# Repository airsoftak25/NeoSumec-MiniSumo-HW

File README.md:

# NeoSumec-MiniSumo-HW

# Description 
In this reposirotry contains: PCB, Gerber, cut files and other stuff about elektronics for our Minisumo robots

|Folder name|what is it|
|:-:|:-|
|MK-1|Contains HW design for our first MiniSumo robot **MK-1**|
|QRE-Boards|Contains HW design for our QRE1113 sensor rigs|

# Contributors
People witch work on some part of HW for our MiniSumo Robots
| Name | Part |
|:-:|:-|
| Vadim Sobčuk | Head of PCB and cut Design |

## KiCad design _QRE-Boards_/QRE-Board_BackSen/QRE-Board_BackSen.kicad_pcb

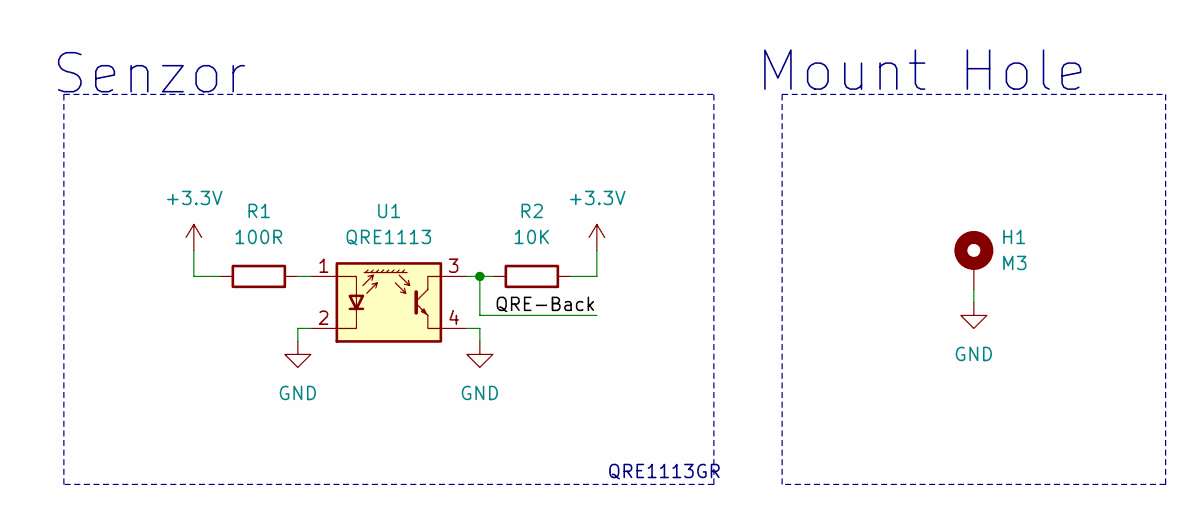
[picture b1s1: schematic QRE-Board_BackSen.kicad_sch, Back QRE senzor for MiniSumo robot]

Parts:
H1: M3; MountingHole_3.2mm_M3_Pad
R1: 100R; R_0805_2012Metric_Pad1.20x1.40mm_HandSolder
R2: 10K; C_0805_2012Metric_Pad1.18x1.45mm_HandSolder
U1: QRE1113; OnSemi_CASE100AQ

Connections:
+3.3V: R1.1, R2.2
/QRE-Back: R2.1, U1.3
GND: H1.1 (1_1), U1.2 (K), U1.4
unnamed: R1.2, U1.1 (A)

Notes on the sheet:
QRE1113GR
Mount Hole
Senzor

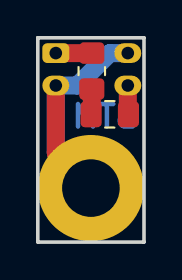
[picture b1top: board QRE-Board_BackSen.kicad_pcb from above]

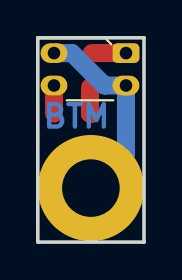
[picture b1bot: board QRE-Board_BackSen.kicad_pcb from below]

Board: 2 copper layers, 5.9 x 11.3 mm, 4 parts (2 on the bottom side), 4 nets.

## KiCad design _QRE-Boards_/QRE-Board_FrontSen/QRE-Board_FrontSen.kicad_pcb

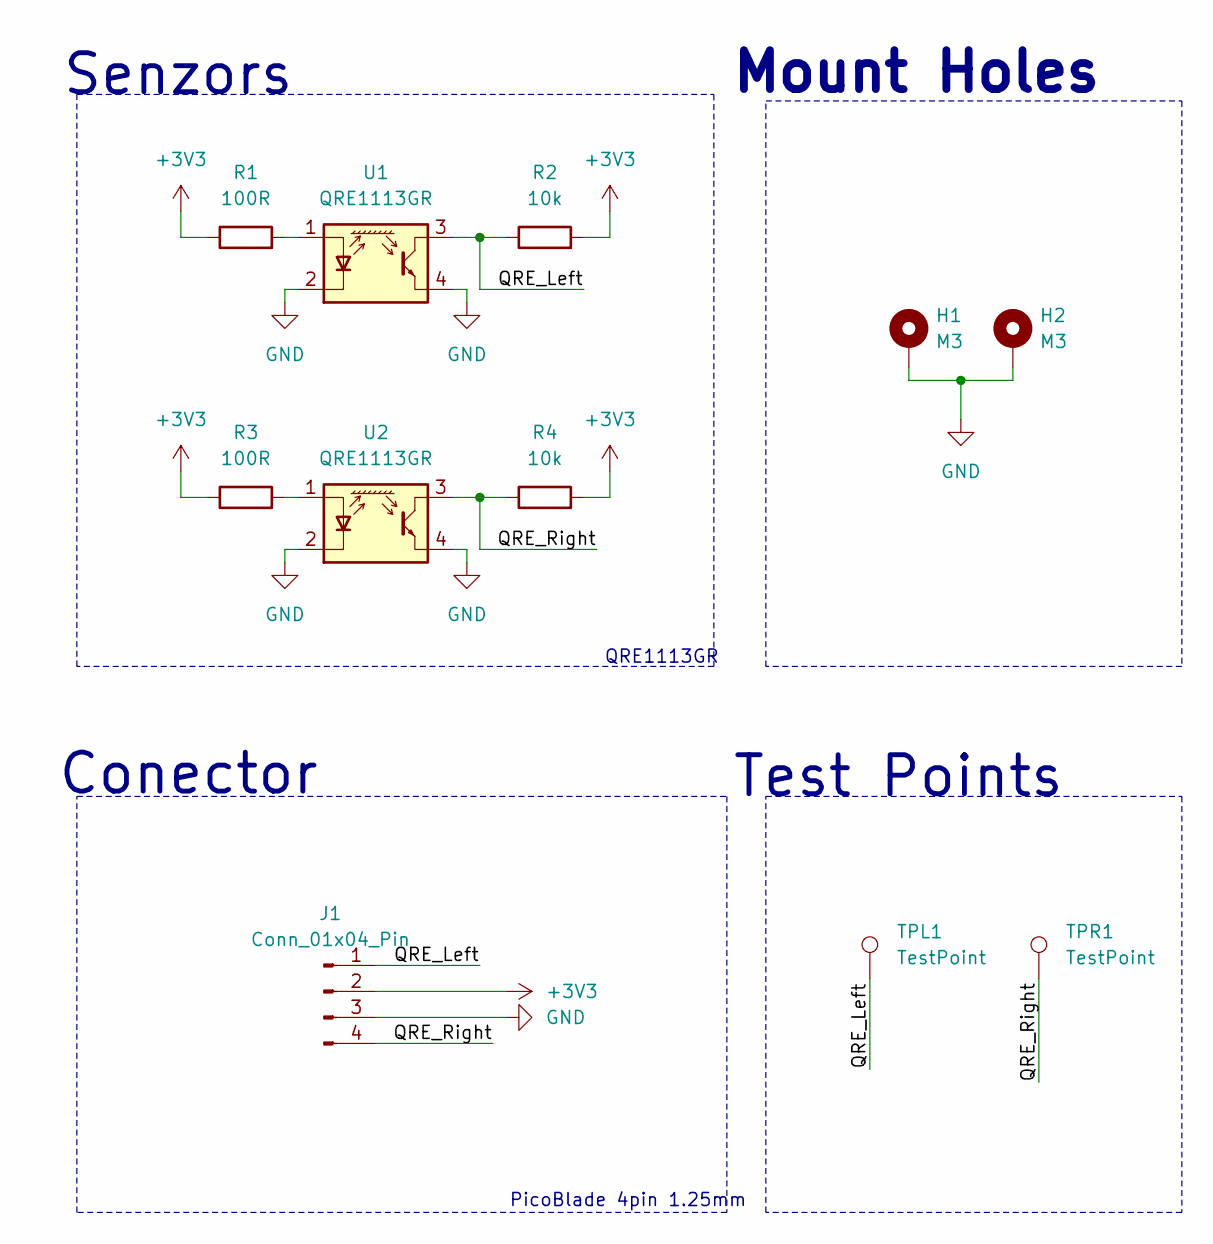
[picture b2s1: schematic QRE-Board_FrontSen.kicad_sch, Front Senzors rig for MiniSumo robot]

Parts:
H1, H2: M3; MountingHole_3.2mm_M3_Pad_Via
J1: Conn_01x04_Pin; Molex_PicoBlade_53261-0471_1x04-1MP_P1.25mm_Horizontal
R1, R3: 100R; R_0805_2012Metric_Pad1.20x1.40mm_HandSolder
R2, R4: 10k; R_0805_2012Metric_Pad1.20x1.40mm_HandSolder
TPL1: TestPoint
TPR1: TestPoint
U1, U2: QRE1113GR; OnSemi_CASE100CY

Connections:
+3V3: J1.2, R1.1, R2.2, R3.1, R4.2
/QRE_Left: J1.1, R2.1, TPL1.1 (1_1), U1.3
/QRE_Right: J1.4, R4.1, TPR1.1 (1_1), U2.3
GND: H1.1 (1_1), H2.1 (1_1), J1.3, U1.2 (K), U1.4, U2.2 (K), U2.4
unnamed: R1.2, U1.1 (A)
unnamed: R3.2, U2.1 (A)

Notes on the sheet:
Mount Holes
Conector
Test Points
PicoBlade 4pin 1.25mm
QRE1113GR
Senzors

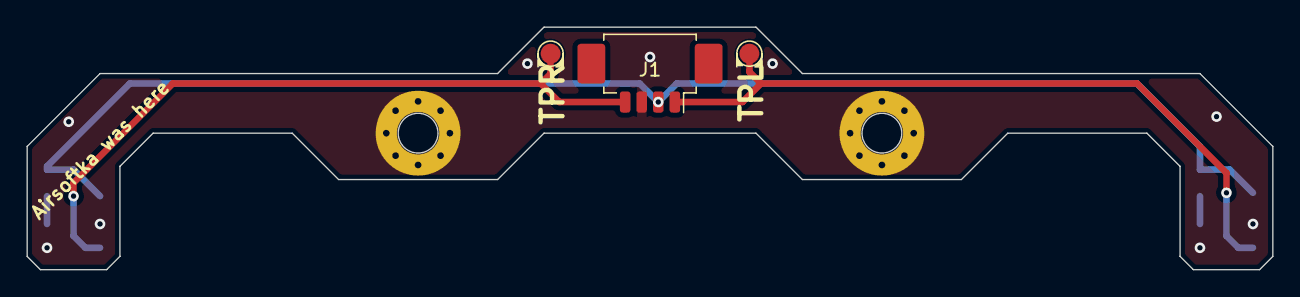
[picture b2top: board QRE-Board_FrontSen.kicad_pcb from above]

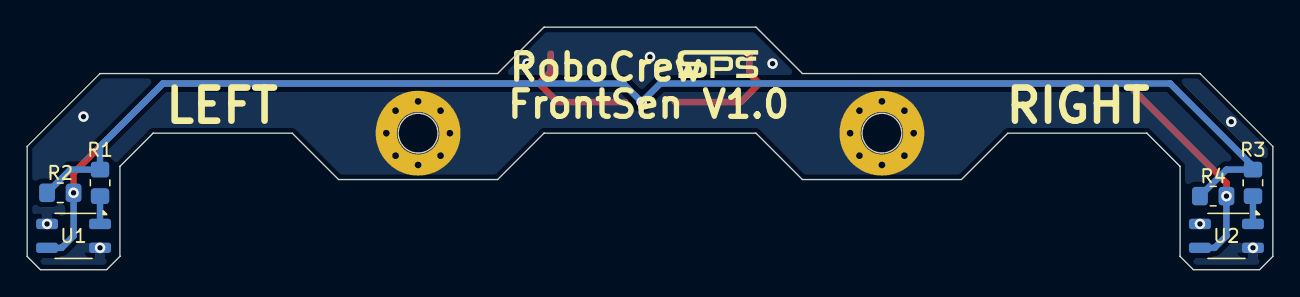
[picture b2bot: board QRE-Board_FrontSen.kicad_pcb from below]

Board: 2 copper layers, 94.0 x 18.3 mm, 11 parts (6 on the bottom side), 6 nets.

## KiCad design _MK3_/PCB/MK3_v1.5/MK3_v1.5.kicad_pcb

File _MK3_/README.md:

# This Folder contains upgrades for MK3(from Team Sumec) maded by Team NeoSumec

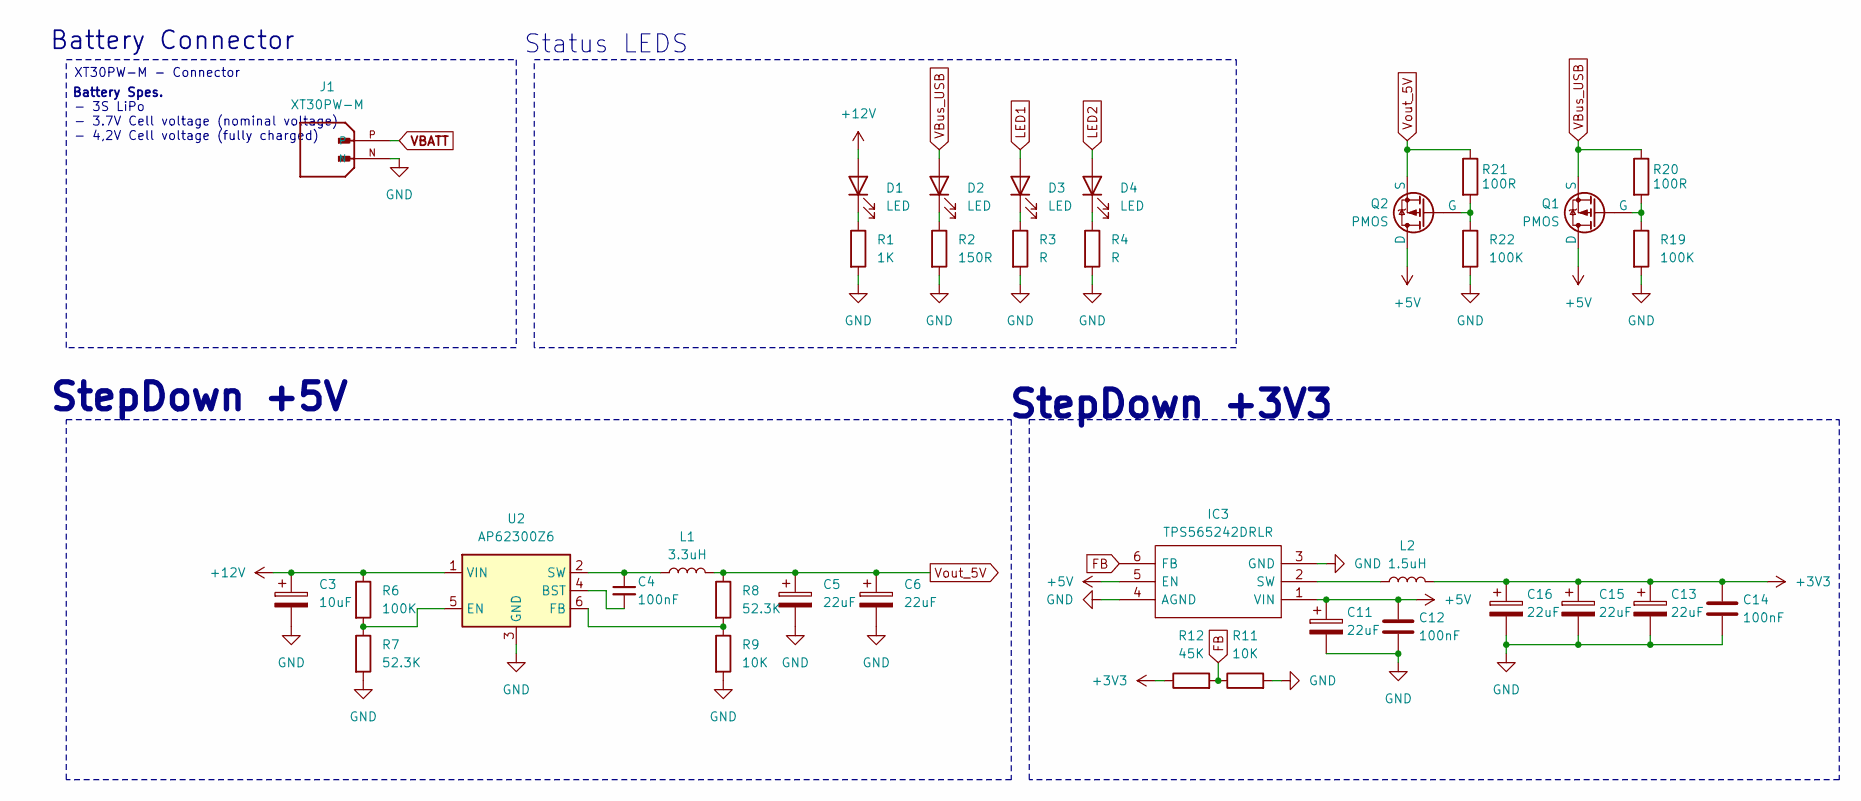
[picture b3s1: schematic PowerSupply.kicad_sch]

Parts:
C3: 10uF; CP_EIA-3216-18_Kemet-A_HandSolder
C4, C12, C14: 100nF; C_0805_2012Metric_Pad1.18x1.45mm_HandSolder
C5, C6, C11, C13, C15, C16: 22uF; CP_EIA-3216-18_Kemet-A_HandSolder
D1, D2, D3, D4: LED; LED_0805_2012Metric_Pad1.15x1.40mm_HandSolder
IC3: TPS565242DRLR; SOT-563; Manufacturer_Part_Number TPS565242DRLR; Mouser Part Number 595-TPS565242DRLR
J1: XT30PW-M; AMASS_XT30PW-M; PARTREV 1.2
L1: 3.3uH; L_Vishay_IHLP-1616
L2: 1.5uH; L_Vishay_IHLP-1212
Q1, Q2: PMOS; SOT-23
R1: 1K; R_0805_2012Metric_Pad1.20x1.40mm_HandSolder
R2: 150R; R_0805_2012Metric_Pad1.20x1.40mm_HandSolder
R3, R4: R; R_0805_2012Metric_Pad1.20x1.40mm_HandSolder
R6, R19, R22: 100K; R_0805_2012Metric_Pad1.20x1.40mm_HandSolder
R7, R8: 52.3K; R_0805_2012Metric_Pad1.20x1.40mm_HandSolder
R9, R11: 10K; R_0805_2012Metric_Pad1.20x1.40mm_HandSolder
R12: 45K; R_0805_2012Metric_Pad1.20x1.40mm_HandSolder
R20, R21: 100R; R_0805_2012Metric_Pad1.20x1.40mm_HandSolder
U2: AP62300Z6; SOT-563

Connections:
+3V3: C13.1, C14.1, C15.1, C16.1, L2.2, R12.1; also elsewhere on the board
+5V: C11.1, C12.1, IC3.1 (VIN), IC3.5 (EN), Q1.1 (D), Q2.1 (D); also elsewhere on the board
+12V: C3.1, D1.2 (A), R6.1, U2.1 (VIN); also elsewhere on the board
FB: IC3.6 (FB), R11.1, R12.2
GND: C3.2, C5.2, C6.2, C11.2, C12.2, C13.2, C14.2, C15.2, C16.2, IC3.3 (GND), IC3.4 (AGND), J1.N, R1.2, R2.2, R3.2, R4.2, R7.2, R9.2, R11.2, R19.2, R22.2, U2.3 (GND); also elsewhere on the board
LED1: D3.2 (A); also elsewhere on the board
LED2: D4.2 (A); also elsewhere on the board
unnamed: D1.1 (K), R1.1
unnamed: D2.1 (K), R2.1
unnamed: D3.1 (K), R3.1
unnamed: D4.1 (K), R4.1
unnamed: IC3.2 (SW), L2.1
unnamed: Q1.2 (G), R19.1, R20.2
unnamed: Q2.2 (G), R21.2, R22.1
unnamed: C4.2, U2.4 (BST)
unnamed: R6.2, R7.1, U2.5 (EN)
unnamed: R8.2, R9.1, U2.6 (FB)
unnamed: C4.1, L1.1, U2.2 (SW)
VBATT: J1.P; also elsewhere on the board
VBus_USB: D2.2 (A), Q1.3 (S), R20.1; also elsewhere on the board
Vout_5V: C5.1, C6.1, L1.2, Q2.3 (S), R8.1, R21.1

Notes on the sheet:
Battery Spes.
StepDown +5V
Battery Connector
Status LEDS
XT30PW-M - Connector
- 3S LiPo - 3.7V Cell voltage (nominal voltage) - 4,2V Cell voltage (fully charged)
StepDown +3V3

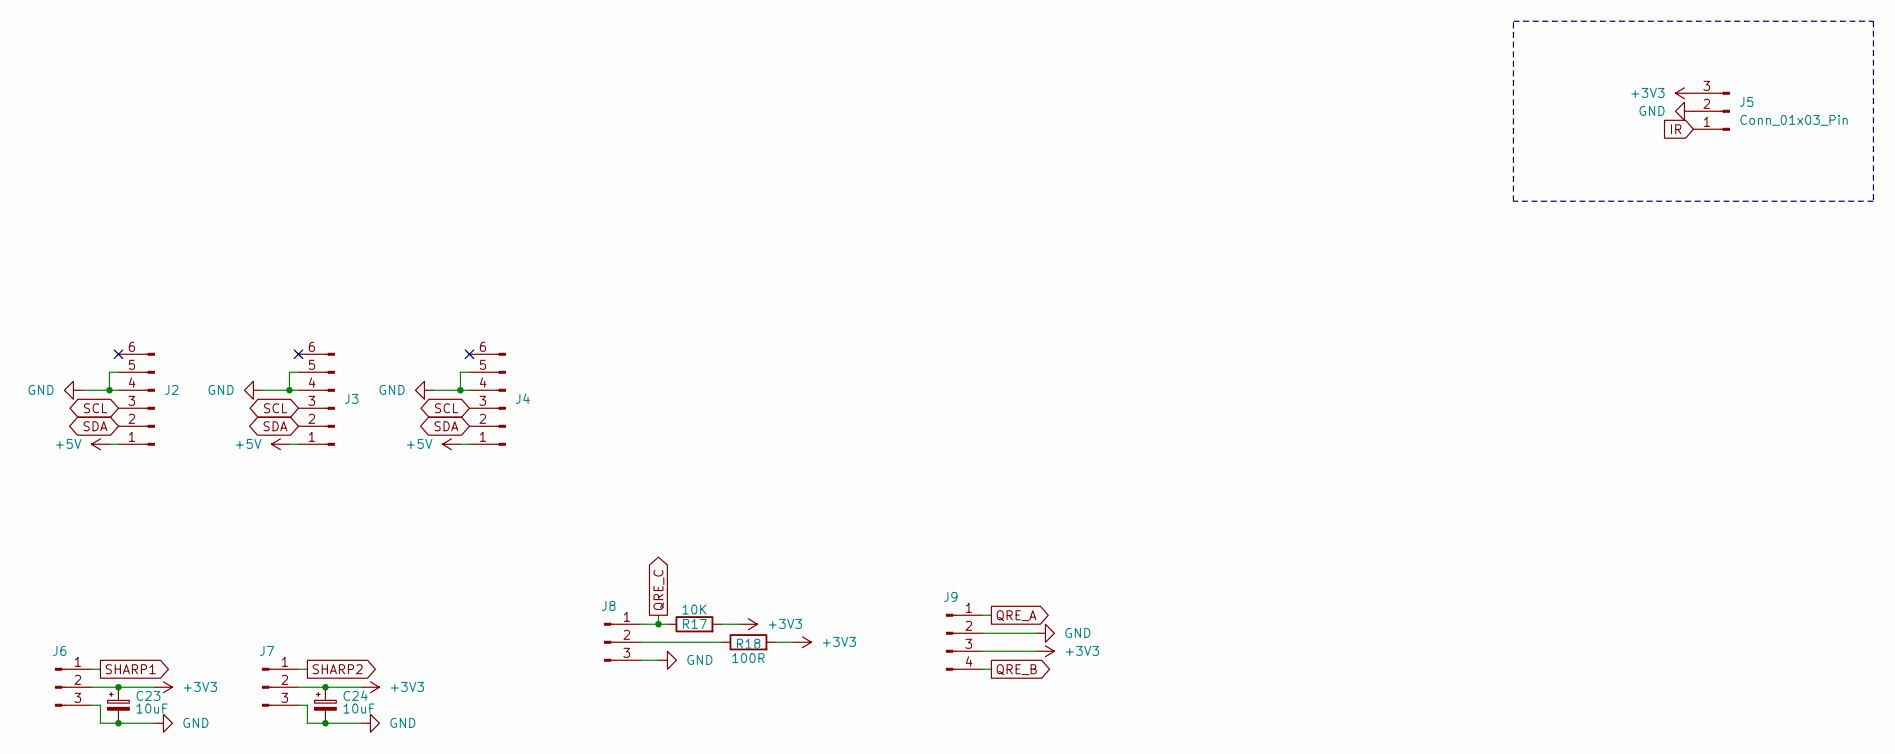
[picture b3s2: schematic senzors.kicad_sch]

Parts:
C23, C24: 10uF; CP_EIA-3216-18_Kemet-A_HandSolder
J2, J3, J4: Conn_01x06_Pin; Molex_PicoBlade_53398-0671_1x06-1MP_P1.25mm_Vertical
J5: Conn_01x03_Pin; PinSocket_1x03_P2.54mm_Vertical
J6, J7, J8: Conn_01x03_Pin; Molex_PicoBlade_53398-0371_1x03-1MP_P1.25mm_Vertical
J9: Conn_01x04_Pin; Molex_PicoBlade_53398-0471_1x04-1MP_P1.25mm_Vertical
R17: 10K; R_0805_2012Metric_Pad1.20x1.40mm_HandSolder
R18: 100R; R_0805_2012Metric_Pad1.20x1.40mm_HandSolder

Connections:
+3V3: C23.1, C24.1, J5.3, J6.2, J7.2, J9.3, R17.2, R18.2; also elsewhere on the board
+5V: J2.1, J3.1, J4.1; also elsewhere on the board
GND: C23.2, C24.2, J2.4, J2.5, J3.4, J3.5, J4.4, J4.5, J5.2, J6.3, J7.3, J8.3, J9.2; also elsewhere on the board
IR: J5.1; also elsewhere on the board
unnamed: J8.2, R18.1
QRE_A: J9.1; also elsewhere on the board
QRE_B: J9.4; also elsewhere on the board
QRE_C: J8.1, R17.1; also elsewhere on the board
SCL: J2.3, J3.3, J4.3; also elsewhere on the board
SDA: J2.2, J3.2, J4.2; also elsewhere on the board
SHARP1: J6.1; also elsewhere on the board
SHARP2: J7.1; also elsewhere on the board

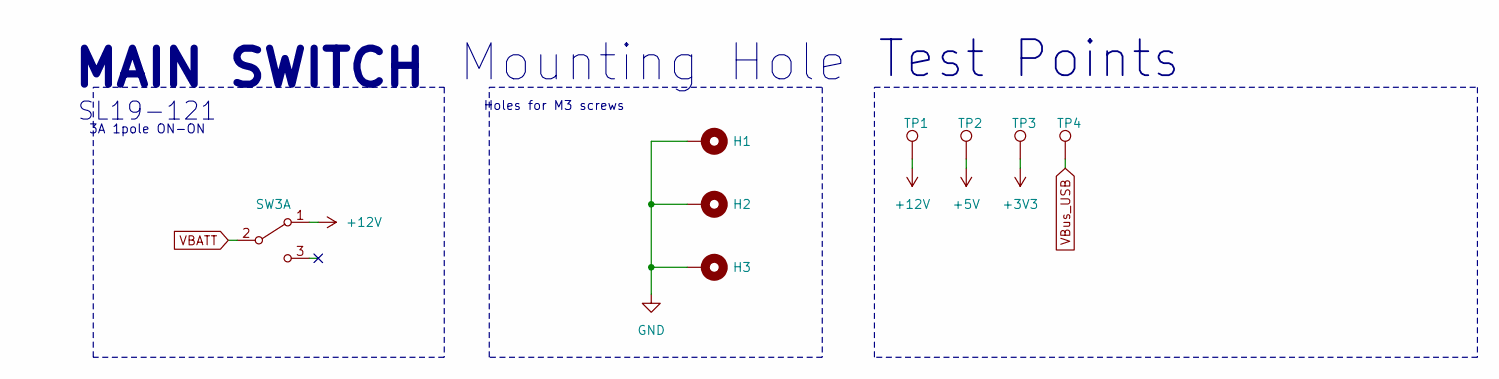
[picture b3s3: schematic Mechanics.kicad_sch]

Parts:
H1, H2, H3: MountingHole_Pad; MountingHole_3.2mm_M3_Pad
SW3: SW_DPDT_x2; 255SB
TP1, TP2, TP3, TP4: TestPoint; TestPoint_Pad_D1.0mm

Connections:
+3V3: TP3.1; also elsewhere on the board
+5V: TP2.1; also elsewhere on the board
+12V: SW3.1 (A), TP1.1; also elsewhere on the board
GND: H1.1, H2.1, H3.1; also elsewhere on the board
VBATT: SW3.2 (B); also elsewhere on the board
VBus_USB: TP4.1; also elsewhere on the board

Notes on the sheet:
3A 1pole ON-ON
Mounting Hole
SL19-121
Holes for M3 screws
Test Points
MAIN SWITCH

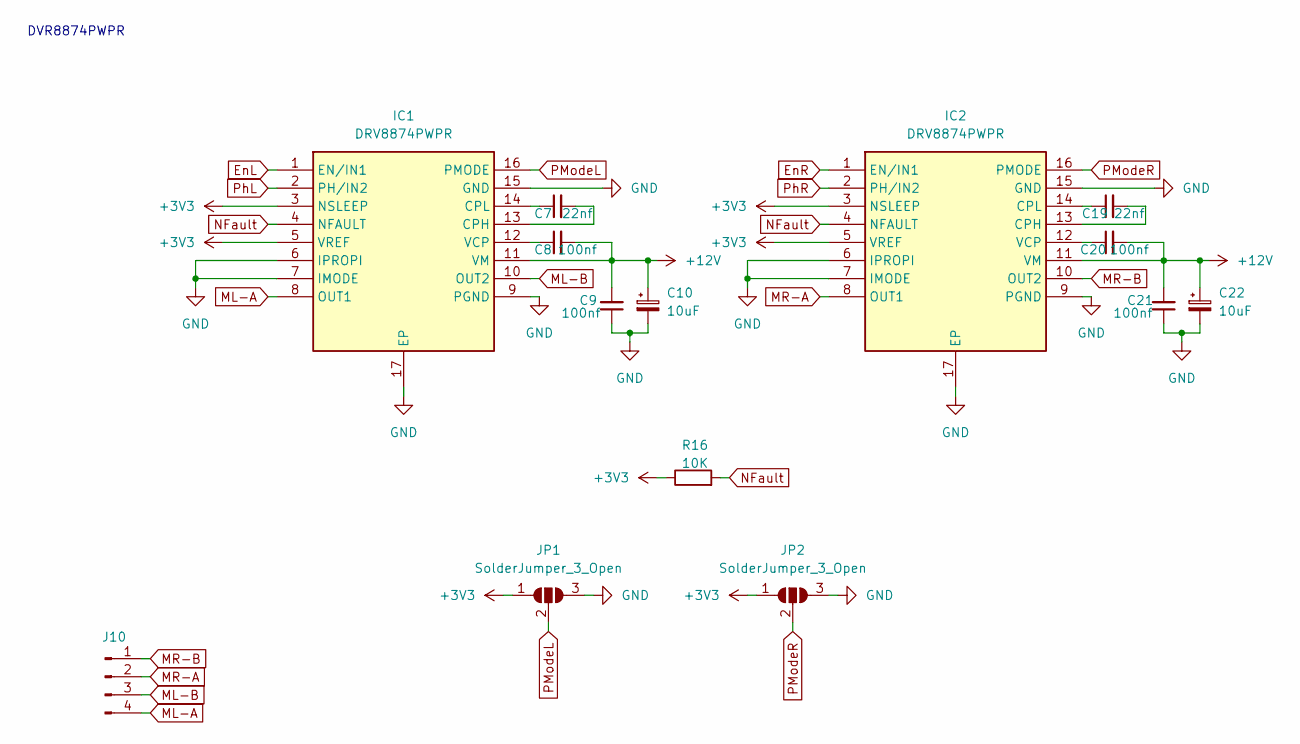
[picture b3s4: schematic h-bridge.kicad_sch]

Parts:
C7, C19: 22nf; C_0805_2012Metric_Pad1.18x1.45mm_HandSolder
C8, C9, C20, C21: 100nf; C_0805_2012Metric_Pad1.18x1.45mm_HandSolder
C10, C22: 10uF; CP_EIA-3216-18_Kemet-A_HandSolder
IC1, IC2: DRV8874PWPR; DRV8874; Manufacturer_Part_Number DRV8874PWPR; Mouser Part Number 595-DRV8874PWPR
J10: Conn_01x04_Pin; JST_XH_B4B-XH-A_1x04_P2.50mm_Vertical
JP1, JP2: SolderJumper_3_Open; SolderJumper-3_P2.0mm_Open_TrianglePad1.0x1.5mm
R16: 10K; R_0805_2012Metric_Pad1.20x1.40mm_HandSolder

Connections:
+3V3: IC1.3 (NSLEEP), IC1.5 (VREF), IC2.3 (NSLEEP), IC2.5 (VREF), JP1.1 (A), JP2.1 (A), R16.1; also elsewhere on the board
+12V: C8.2, C9.2, C10.1, C20.2, C21.2, C22.1, IC1.11 (VM), IC2.11 (VM); also elsewhere on the board
EnL: IC1.1 (EN/IN1); also elsewhere on the board
EnR: IC2.1 (EN/IN1); also elsewhere on the board
GND: C9.1, C10.2, C21.1, C22.2, IC1.6 (IPROPI), IC1.7 (IMODE), IC1.9 (PGND), IC1.15 (GND), IC1.17 (EP), IC2.6 (IPROPI), IC2.7 (IMODE), IC2.9 (PGND), IC2.15 (GND), IC2.17 (EP), JP1.3 (B), JP2.3 (B); also elsewhere on the board
ML-A: IC1.8 (OUT1), J10.4
ML-B: IC1.10 (OUT2), J10.3
MR-A: IC2.8 (OUT1), J10.2
MR-B: IC2.10 (OUT2), J10.1
NFault: IC1.4 (NFAULT), IC2.4 (NFAULT), R16.2; also elsewhere on the board
unnamed: C7.2, IC1.13 (CPH)
unnamed: C7.1, IC1.14 (CPL)
unnamed: C8.1, IC1.12 (VCP)
unnamed: C19.2, IC2.13 (CPH)
unnamed: C19.1, IC2.14 (CPL)
unnamed: C20.1, IC2.12 (VCP)
PModeL: IC1.16 (PMODE), JP1.2 (C)
PModeR: IC2.16 (PMODE), JP2.2 (C)
PhL: IC1.2 (PH/IN2); also elsewhere on the board
PhR: IC2.2 (PH/IN2); also elsewhere on the board

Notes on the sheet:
DVR8874PWPR

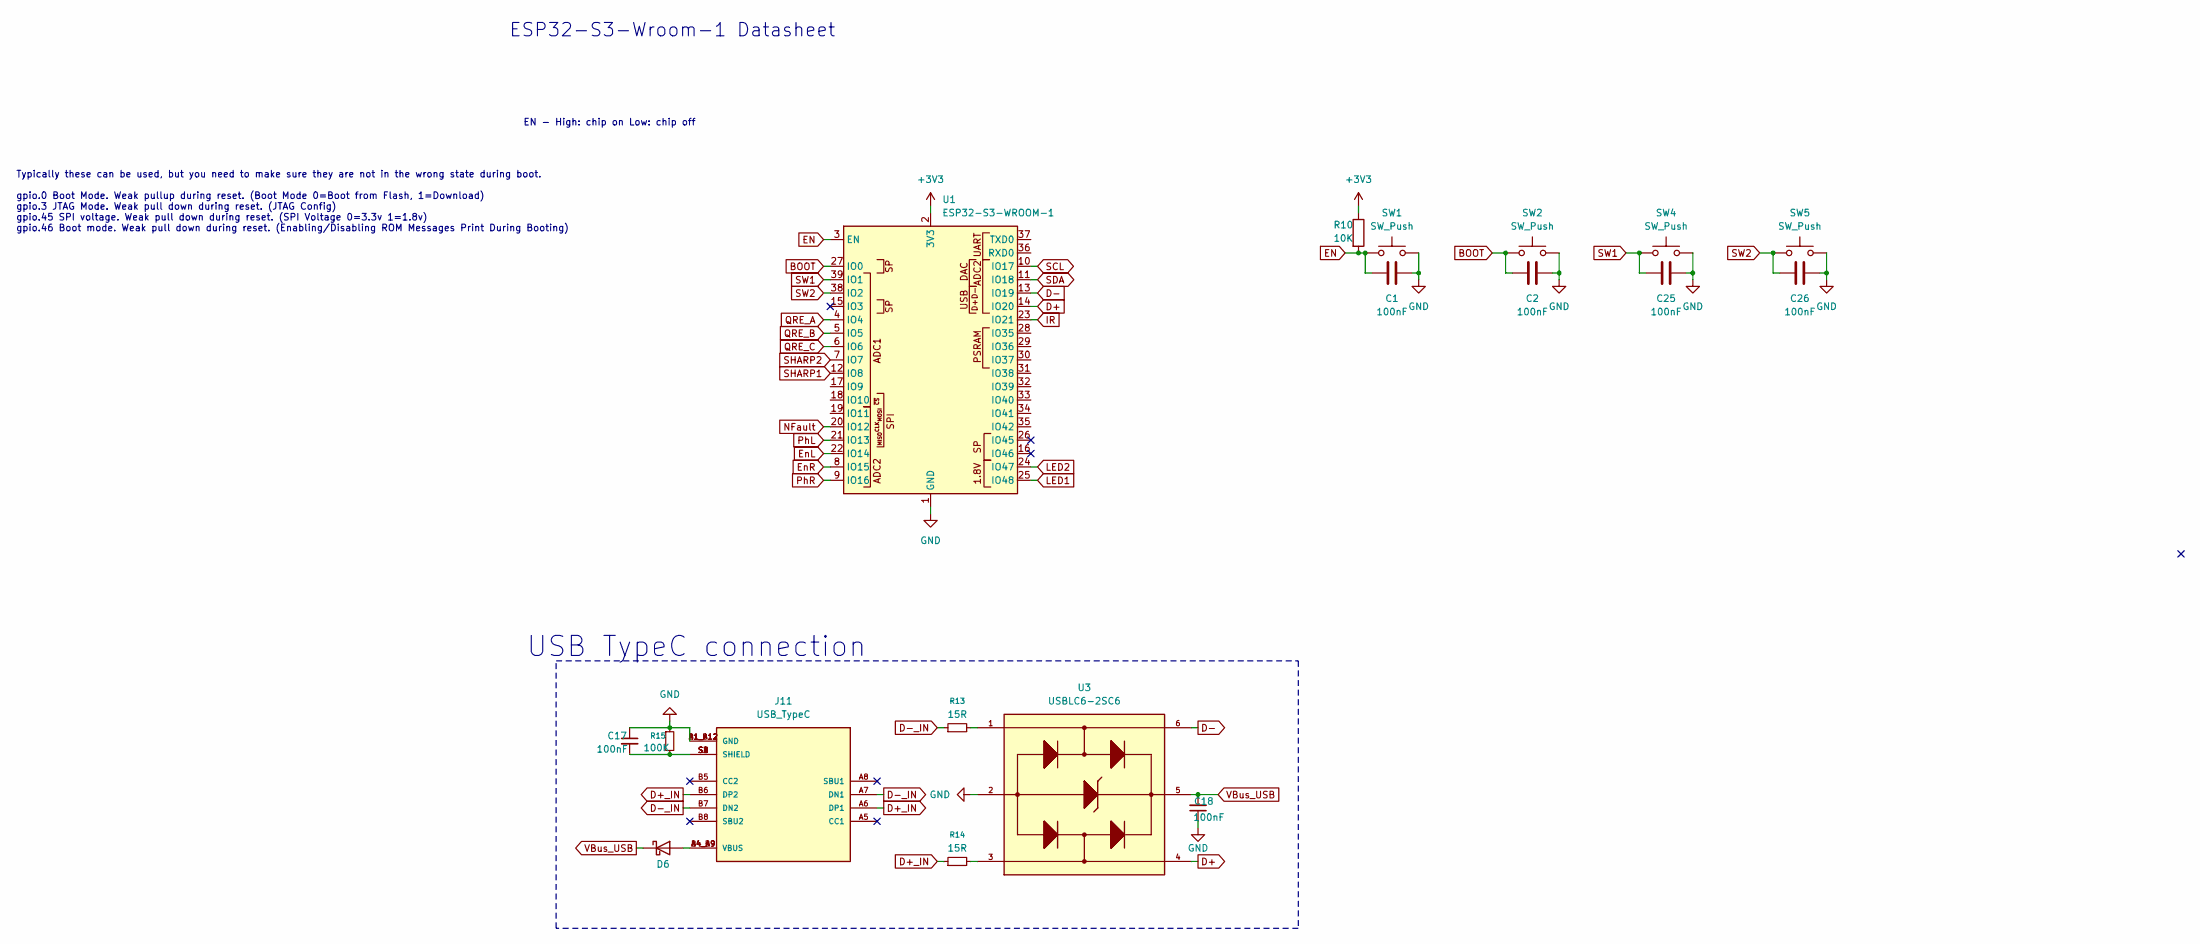
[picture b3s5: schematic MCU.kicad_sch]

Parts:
C1, C2, C17, C18, C25, C26: 100nF; C_0805_2012Metric_Pad1.18x1.45mm_HandSolder
D6: D_Schottky; D_1206_3216Metric_Pad1.42x1.75mm_HandSolder
J11: USB_TypeC; HRO_TYPE-C-31-M-12; PARTREV 2020.12.08
R10: 10K; R_0805_2012Metric_Pad1.20x1.40mm_HandSolder
R13, R14: 15R; R_0805_2012Metric_Pad1.20x1.40mm_HandSolder
R15: 100K; R_0805_2012Metric_Pad1.20x1.40mm_HandSolder
SW1, SW2, SW4, SW5: SW_Push; SW_TL3365AF180QG
U1: ESP32-S3-WROOM-1; XCVR_ESP32-S3-WROOM-1-N8
U3: USBLC6-2SC6; SOT-23-6

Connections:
+3V3: R10.1, U1.2 (3V3); also elsewhere on the board
BOOT: C2.2, SW2.1, U1.27 (IO0)
D+: U1.14 (IO20), U3.4
D+_IN: J11.A6 (DP1), J11.B6 (DP2), R14.1
D-: U1.13 (IO19), U3.6
D-_IN: J11.A7 (DN1), J11.B7 (DN2), R13.1
EN: C1.2, R10.2, SW1.1, U1.3 (EN)
EnL: U1.22 (IO14); also elsewhere on the board
EnR: U1.8 (IO15); also elsewhere on the board
GND: C1.1, C2.1, C17.1, C18.1, C25.1, C26.1, J11.A1_B12 (GND), J11.B1_A12 (GND), R15.1, SW1.2, SW2.2, SW4.2, SW5.2, U1.1 (GND), U1.40 (GND), U1.41 (GND), U3.2; also elsewhere on the board
IR: U1.23 (IO21); also elsewhere on the board
LED1: U1.25 (IO48); also elsewhere on the board
LED2: U1.24 (IO47); also elsewhere on the board
NFault: U1.20 (IO12); also elsewhere on the board
unnamed: C17.2, J11.S1 (SHIELD), J11.S2 (SHIELD), J11.S3 (SHIELD), J11.S4 (SHIELD), R15.2
unnamed: D6.2 (A), J11.A4_B9 (VBUS), J11.B4_A9 (VBUS)
unnamed: R13.2, U3.1
unnamed: R14.2, U3.3
PhL: U1.21 (IO13); also elsewhere on the board
PhR: U1.9 (IO16); also elsewhere on the board
QRE_A: U1.4 (IO4); also elsewhere on the board
QRE_B: U1.5 (IO5); also elsewhere on the board
QRE_C: U1.6 (IO6); also elsewhere on the board
SCL: U1.10 (IO17); also elsewhere on the board
SDA: U1.11 (IO18); also elsewhere on the board
SHARP1: U1.12 (IO8); also elsewhere on the board
SHARP2: U1.7 (IO7); also elsewhere on the board
SW1: C25.2, SW4.1, U1.39 (IO1)
SW2: C26.2, SW5.1, U1.38 (IO2)
VBus_USB: C18.2, D6.1 (K), U3.5; also elsewhere on the board

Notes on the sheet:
ESP32-S3-Wroom-1 Datasheet
EN - High: chip on Low: chip off
USB TypeC connection
Typically these can be used, but you need to make sure they are not in the wrong state during boot. gpio.0 Boot Mode. Weak pullup during reset. (Boot Mode 0=Boot from Flash, 1=Download) gpio.3 JTAG Mode. Weak pull down during reset. (JTAG Config) gpio.45 SPI voltage. Weak pull down during reset. (S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

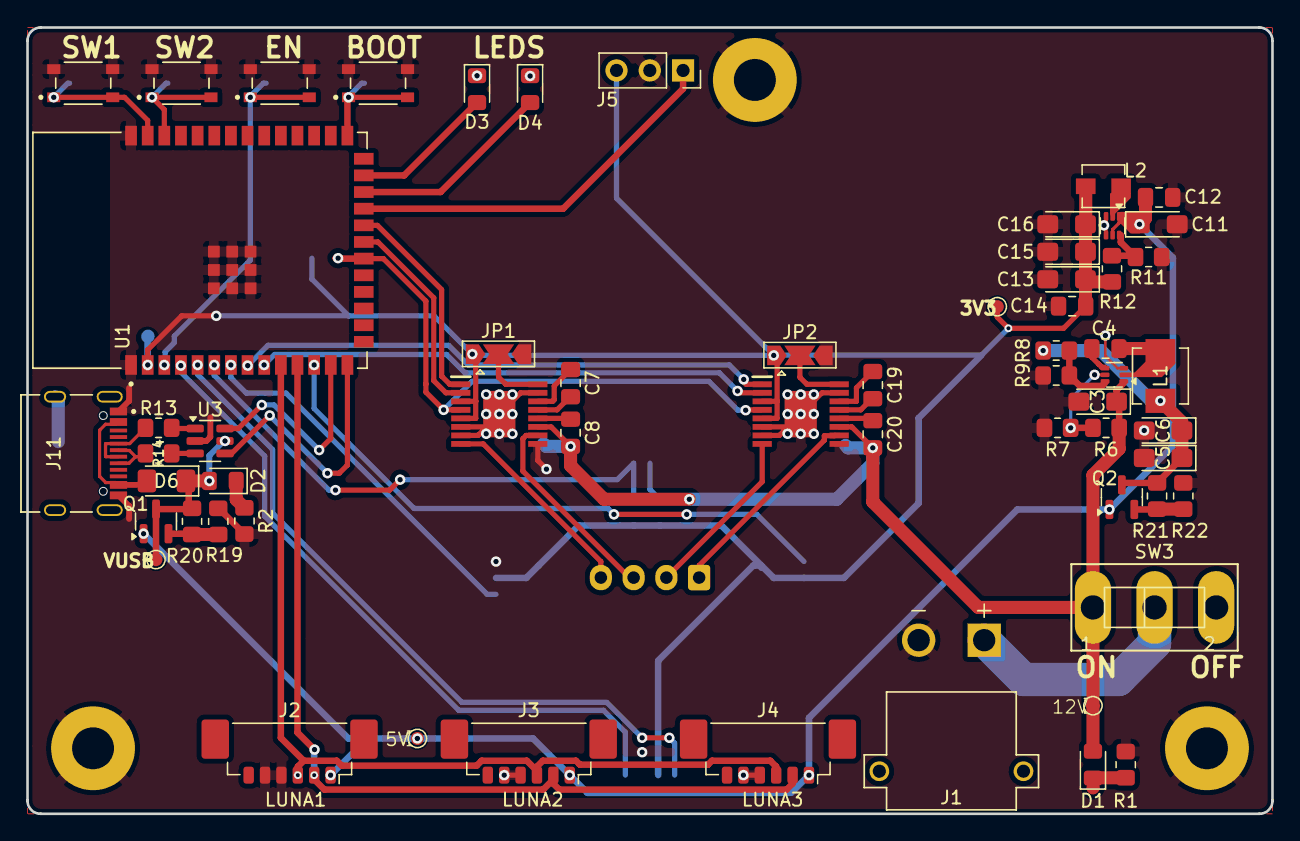
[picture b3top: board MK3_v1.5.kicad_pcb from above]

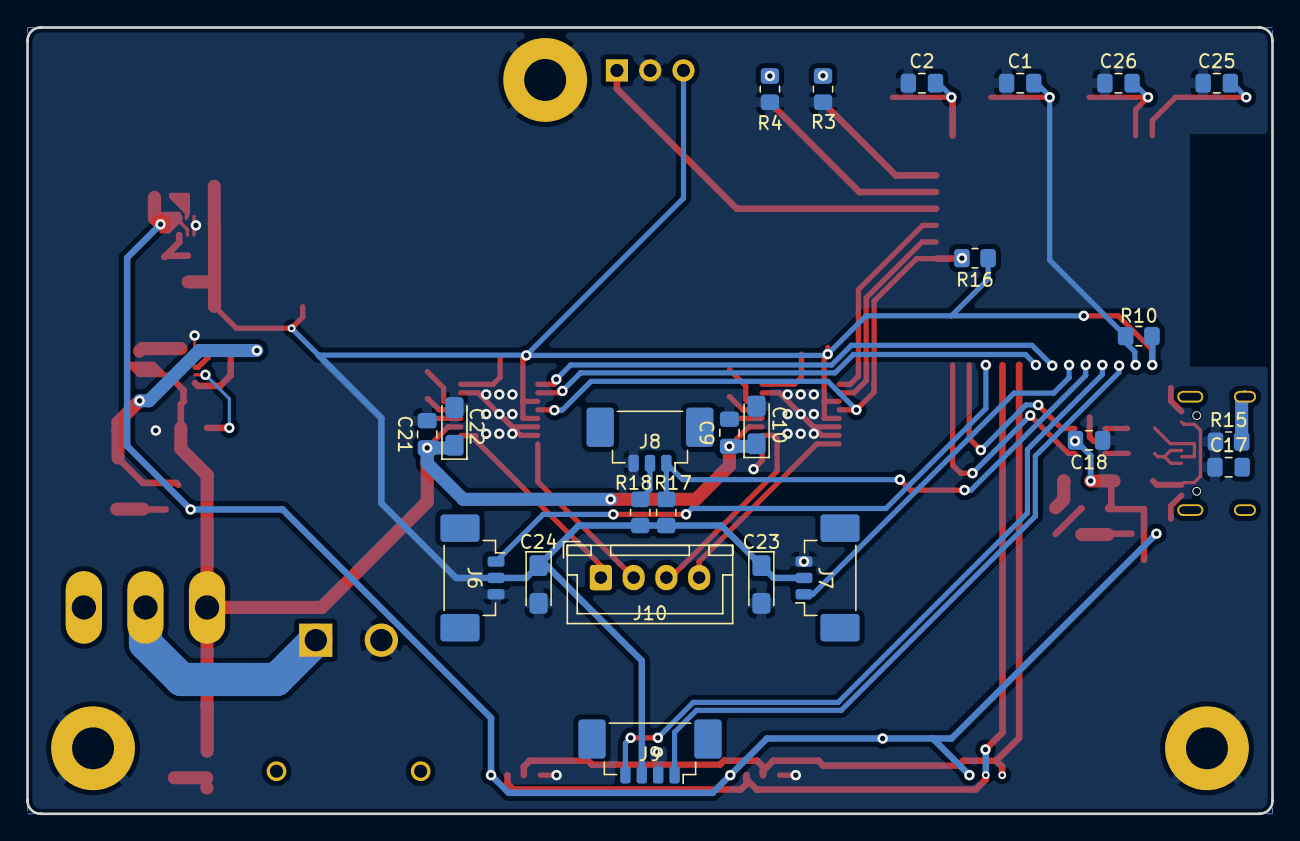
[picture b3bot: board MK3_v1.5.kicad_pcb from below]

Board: 2 copper layers, 95.0 x 60.0 mm, 87 parts (24 on the bottom side), 59 nets.

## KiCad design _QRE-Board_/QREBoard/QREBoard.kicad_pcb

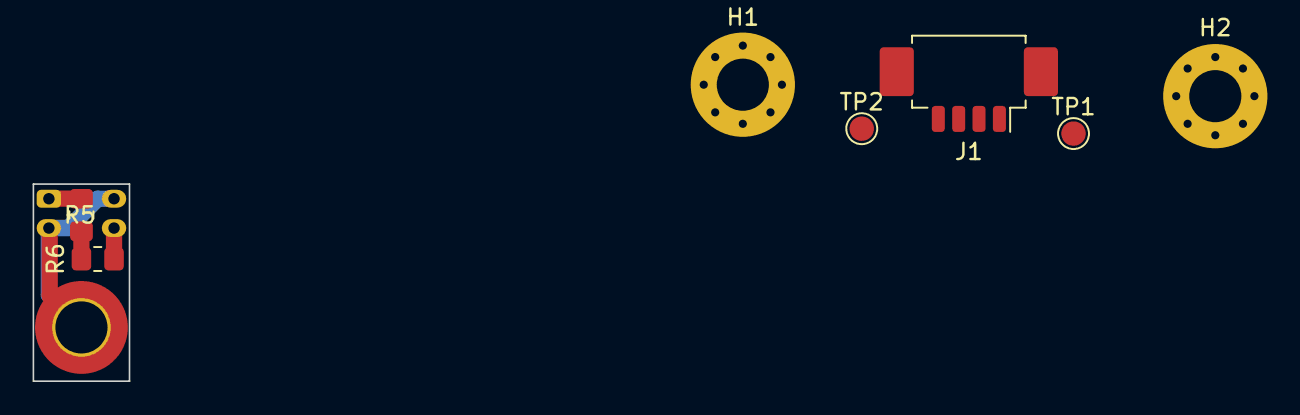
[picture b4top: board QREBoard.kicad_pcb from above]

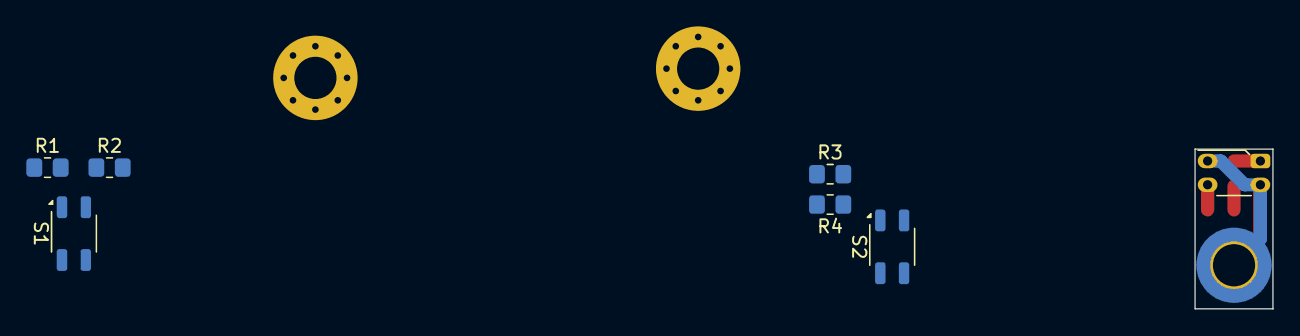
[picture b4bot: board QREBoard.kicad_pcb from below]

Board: 2 copper layers, 15 parts (7 on the bottom side), 8 nets.

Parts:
H1, H2: M3; MountingHole_3.2mm_M3_Pad_Via
H3: M3; MountingHole_3.2mm_M3_ISO7380_Pad_TopBottom
J1: Conn_01x04_Pin; Molex_PicoBlade_53261-0471_1x04-1MP_P1.25mm_Horizontal
R1, R3, R5: 100R; R_0805_2012Metric_Pad1.20x1.40mm_HandSolder
R2, R4, R6: 10K; R_0805_2012Metric_Pad1.20x1.40mm_HandSolder
S1, S2: QRE1113GR; OnSemi_CASE100CY
S3: QRE1113; OnSemi_CASE100AQ
TP1: QRE_Left; TestPoint_Pad_D1.5mm
TP2: QRE_Right; TestPoint_Pad_D1.5mm

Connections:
+3V3: J1.2, R1.1, R2.2, R3.1, R4.2, R5.1, R6.2
GND: H1.1 (1_1), H2.1 (1_1), H3.1 (1_1), J1.3, S1.2 (K), S1.4, S2.2 (K), S2.4, S3.2 (K), S3.4
unnamed: R1.2, S1.1 (A)
unnamed: R3.2, S2.1 (A)
unnamed: R5.2, S3.1 (A)
QRE_Back: R6.1, S3.3
QRE_Left: J1.1, R2.1, S1.3, TP1.1 (1_1)
QRE_Right: J1.4, R4.1, S2.3, TP2.1 (1_1)

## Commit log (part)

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2025-12-27 First push
    this contain gitnore, preparation for updates and other stuff
2026-01-03 MK3_v1.5
    work in progress
2026-01-04 PCB UPDATE
2026-01-07 pcb done
2026-02-10 some changes
2026-03-21 README.md Update
2026-03-22 Create MK-1
2026-03-30 .gitignore
2026-04-06 Added QRE Board and features list for MK-1
2026-04-06 Fix formatting in README.md features list
2026-06-04 QRE-BOARD UPDATE
    Redesighned QRE-BackSen to maxbe latest eteration for now
    Added some changes on mk-1 DPS desighn too (Not that much)
